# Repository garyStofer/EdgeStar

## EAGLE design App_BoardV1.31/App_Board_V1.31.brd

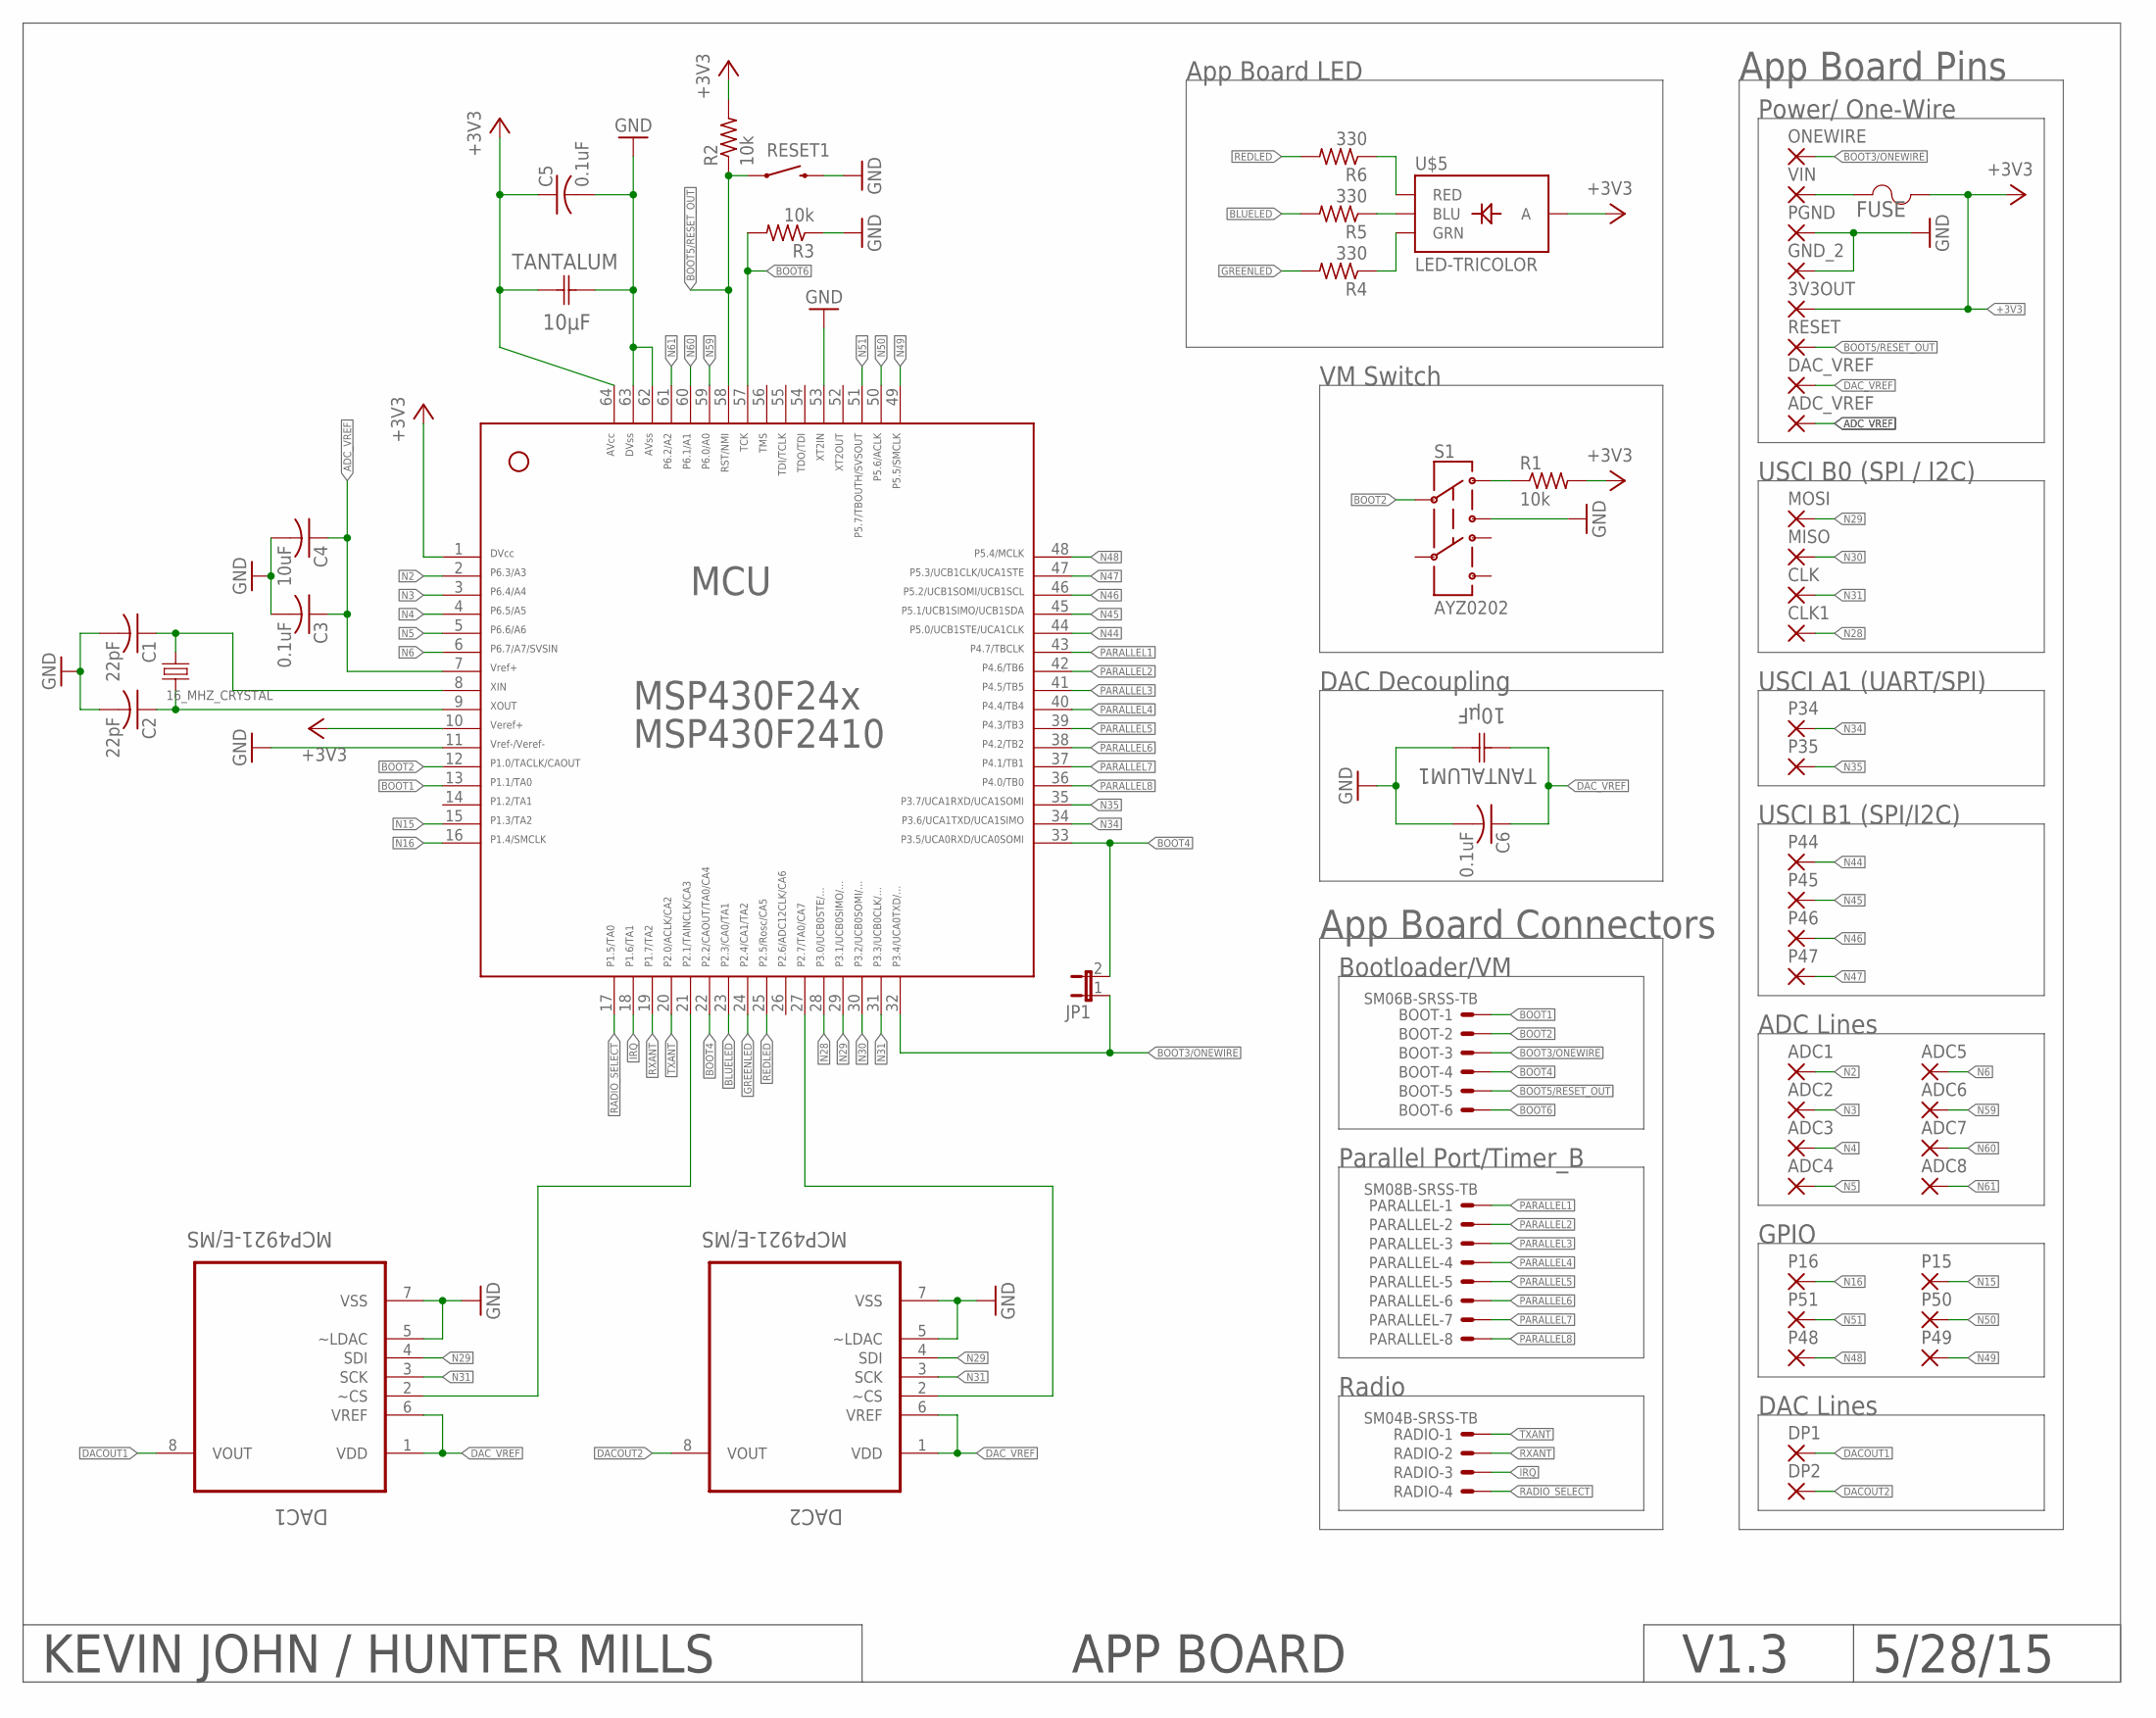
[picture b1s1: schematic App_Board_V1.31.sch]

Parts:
3V3OUT: 1,6/0,9
16_MHZ_CRYSTAL: HUNTERCRYSTAL; CRYSTAL-SMD-5X3
ADC1, ADC2, ADC3, ADC4, ADC5, ADC6, ADC7, ADC8: 1,6/0,9
ADC_VREF: 1,6/0,9
BOOT: SM06B-SRSS-TB
C1, C2: 22pF; C0805
C3, C5, C6: 0.1uF; C0805
C4: 10uF; C0805
CLK, CLK1: 1,6/0,9
DAC1, DAC2: MCP4921-E/MS; SOP65P490X110-8N
DAC_VREF: 1,6/0,9
DP1, DP2: 1,6/0,9
FUSE: HUNTERFUSE; CAPC4532X254N
GND_2: 1,6/0,9
JP1: JP1E; JP1
MCU: F24[X/10]---PM64; PM/PAG64
MISO: 1,6/0,9
MOSI: 1,6/0,9
ONEWIRE: 1,6/0,9
P15, P16, P34, P35, P44, P45, P46, P47, P48, P49, P50, P51: 1,6/0,9
PARALLEL: SM08B-SRSS-TB
PGND: 1,6/0,9
R1, R2, R3: 10k; R0603
R4, R5, R6: 330; R0603
RADIO: SM04B-SRSS-TB
RESET: 1,6/0,9
RESET1: SWITCH-MOMENTARY-2SMD; TACTILE-SWITCH-SMD
S1: AYZ0202
TANTALUM, TANTALUM1: 10µF; CAPCP3528X120N
U$5: LED-TRICOLOR; LED-TRICOLOR-SMD
VIN: 1,6/0,9

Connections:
3.3VOUT: FUSE.1, VIN.1
+3V3: 3V3OUT.1, C5.1, FUSE.2, MCU.1, MCU.10, MCU.64, R1.2, R2.2, TANTALUM.1 (C1), U$5.A
ADC_VREF: ADC_VREF.1, C3.1, C4.1, MCU.7
BLUELED: MCU.23, R5.2
BOOT1: BOOT.1, MCU.13
BOOT2: BOOT.2, MCU.12, S1.2
BOOT3/ONEWIRE: BOOT.3, JP1.1, MCU.32, ONEWIRE.1
BOOT4: BOOT.4, JP1.2, MCU.22, MCU.33
BOOT5/RESET_OUT: BOOT.5, MCU.58, R2.1, RESET.1, RESET1.1
BOOT6: BOOT.6, MCU.57, R3.2
DACOUT1: DAC1.8 (VOUT), DP1.1
DACOUT2: DAC2.8 (VOUT), DP2.1
DAC_VREF: C6.1, DAC1.1 (VDD), DAC1.6 (VREF), DAC2.1 (VDD), DAC2.6 (VREF), DAC_VREF.1, TANTALUM1.1 (C1)
GND: C1.2, C2.2, C3.2, C4.2, C5.2, C6.2, DAC1.5 (~LDAC), DAC1.7 (VSS), DAC2.5 (~LDAC), DAC2.7 (VSS), GND_2.1, MCU.11, MCU.53, MCU.62, MCU.63, PGND.1, R3.1, RESET1.3 (2), S1.1 (3), TANTALUM.2 (C2), TANTALUM1.2 (C2)
GREENLED: MCU.24, R4.2
IRQ: MCU.18, RADIO.3
N2: ADC1.1, MCU.2
N3: ADC2.1, MCU.3
N4: ADC3.1, MCU.4
N5: ADC4.1, MCU.5
N6: ADC5.1, MCU.6
N15: MCU.15, P15.1
N16: MCU.16, P16.1
N28: CLK1.1, MCU.28
N29: DAC1.4 (SDI), DAC2.4 (SDI), MCU.29, MOSI.1
N30: MCU.30, MISO.1
N31: CLK.1, DAC1.3 (SCK), DAC2.3 (SCK), MCU.31
N34: MCU.34, P34.1
N35: MCU.35, P35.1
N44: MCU.44, P44.1
N45: MCU.45, P45.1
N46: MCU.46, P46.1
N47: MCU.47, P47.1
N48: MCU.48, P48.1
N49: MCU.49, P49.1
N50: MCU.50, P50.1
N51: MCU.51, P51.1
N59: ADC6.1, MCU.59
N60: ADC7.1, MCU.60
N61: ADC8.1, MCU.61
unnamed: 16_MHZ_CRYSTAL.3, C1.1, MCU.8
unnamed: 16_MHZ_CRYSTAL.1, C2.1, MCU.9
unnamed: R1.1, S1.3 (1)
unnamed: R5.1, U$5.B (BLU)
unnamed: R6.1, U$5.R (RED)
unnamed: R4.1, U$5.G (GRN)
unnamed: DAC1.2 (~CS), MCU.21
unnamed: DAC2.2 (~CS), MCU.27
PARALLEL1: MCU.43, PARALLEL.1
PARALLEL2: MCU.42, PARALLEL.2
PARALLEL3: MCU.41, PARALLEL.3
PARALLEL4: MCU.40, PARALLEL.4
PARALLEL5: MCU.39, PARALLEL.5
PARALLEL6: MCU.38, PARALLEL.6
PARALLEL7: MCU.37, PARALLEL.7
PARALLEL8: MCU.36, PARALLEL.8
RADIO_SELECT: MCU.17, RADIO.4
REDLED: MCU.25, R6.2
RXANT: MCU.19, RADIO.2
TXANT: MCU.20, RADIO.1

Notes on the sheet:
KEVIN JOHN / HUNTER MILLS
APP BOARD
V1.3
5/28/15
Power/ One-Wire
ADC Lines
DAC Lines
USCI B0 (SPI / I2C)
USCI A1 (UART/SPI)
USCI B1 (SPI/I2C)
GPIO
App Board Pins
Bootloader/VM
Parallel Port/Timer_B
Radio
App Board Connectors
App Board LED
VM Switch
DAC Decoupling

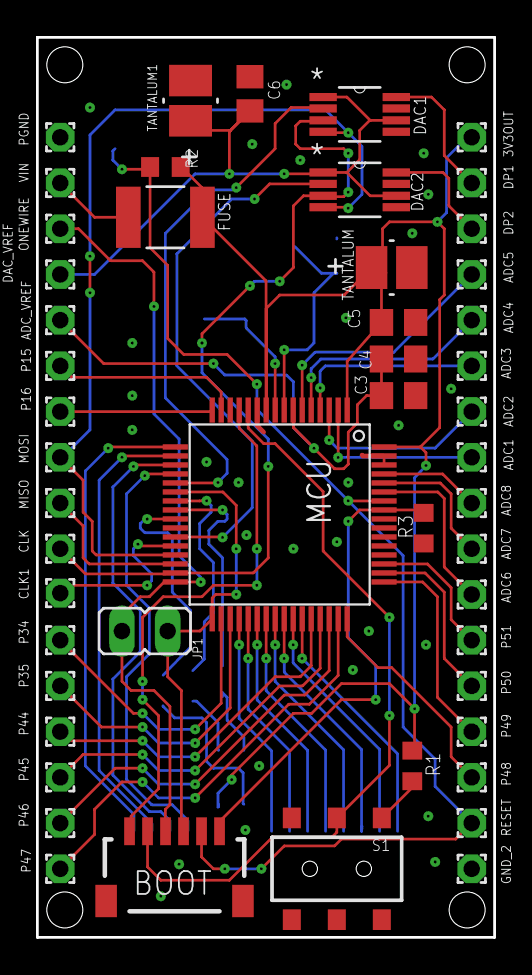
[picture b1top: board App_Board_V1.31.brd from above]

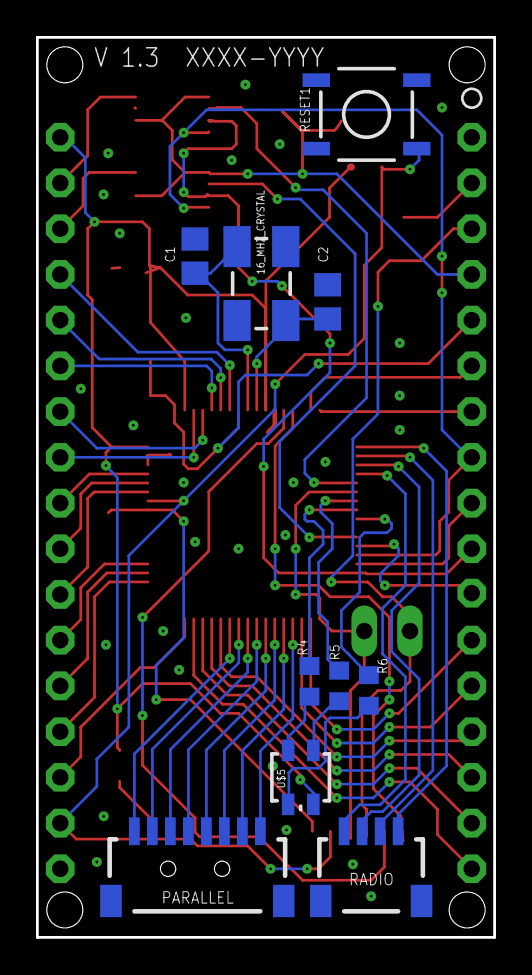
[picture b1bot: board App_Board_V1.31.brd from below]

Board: 2 copper layers, 25.4 x 50.0 mm, 60 parts (10 on the bottom side), 60 nets.

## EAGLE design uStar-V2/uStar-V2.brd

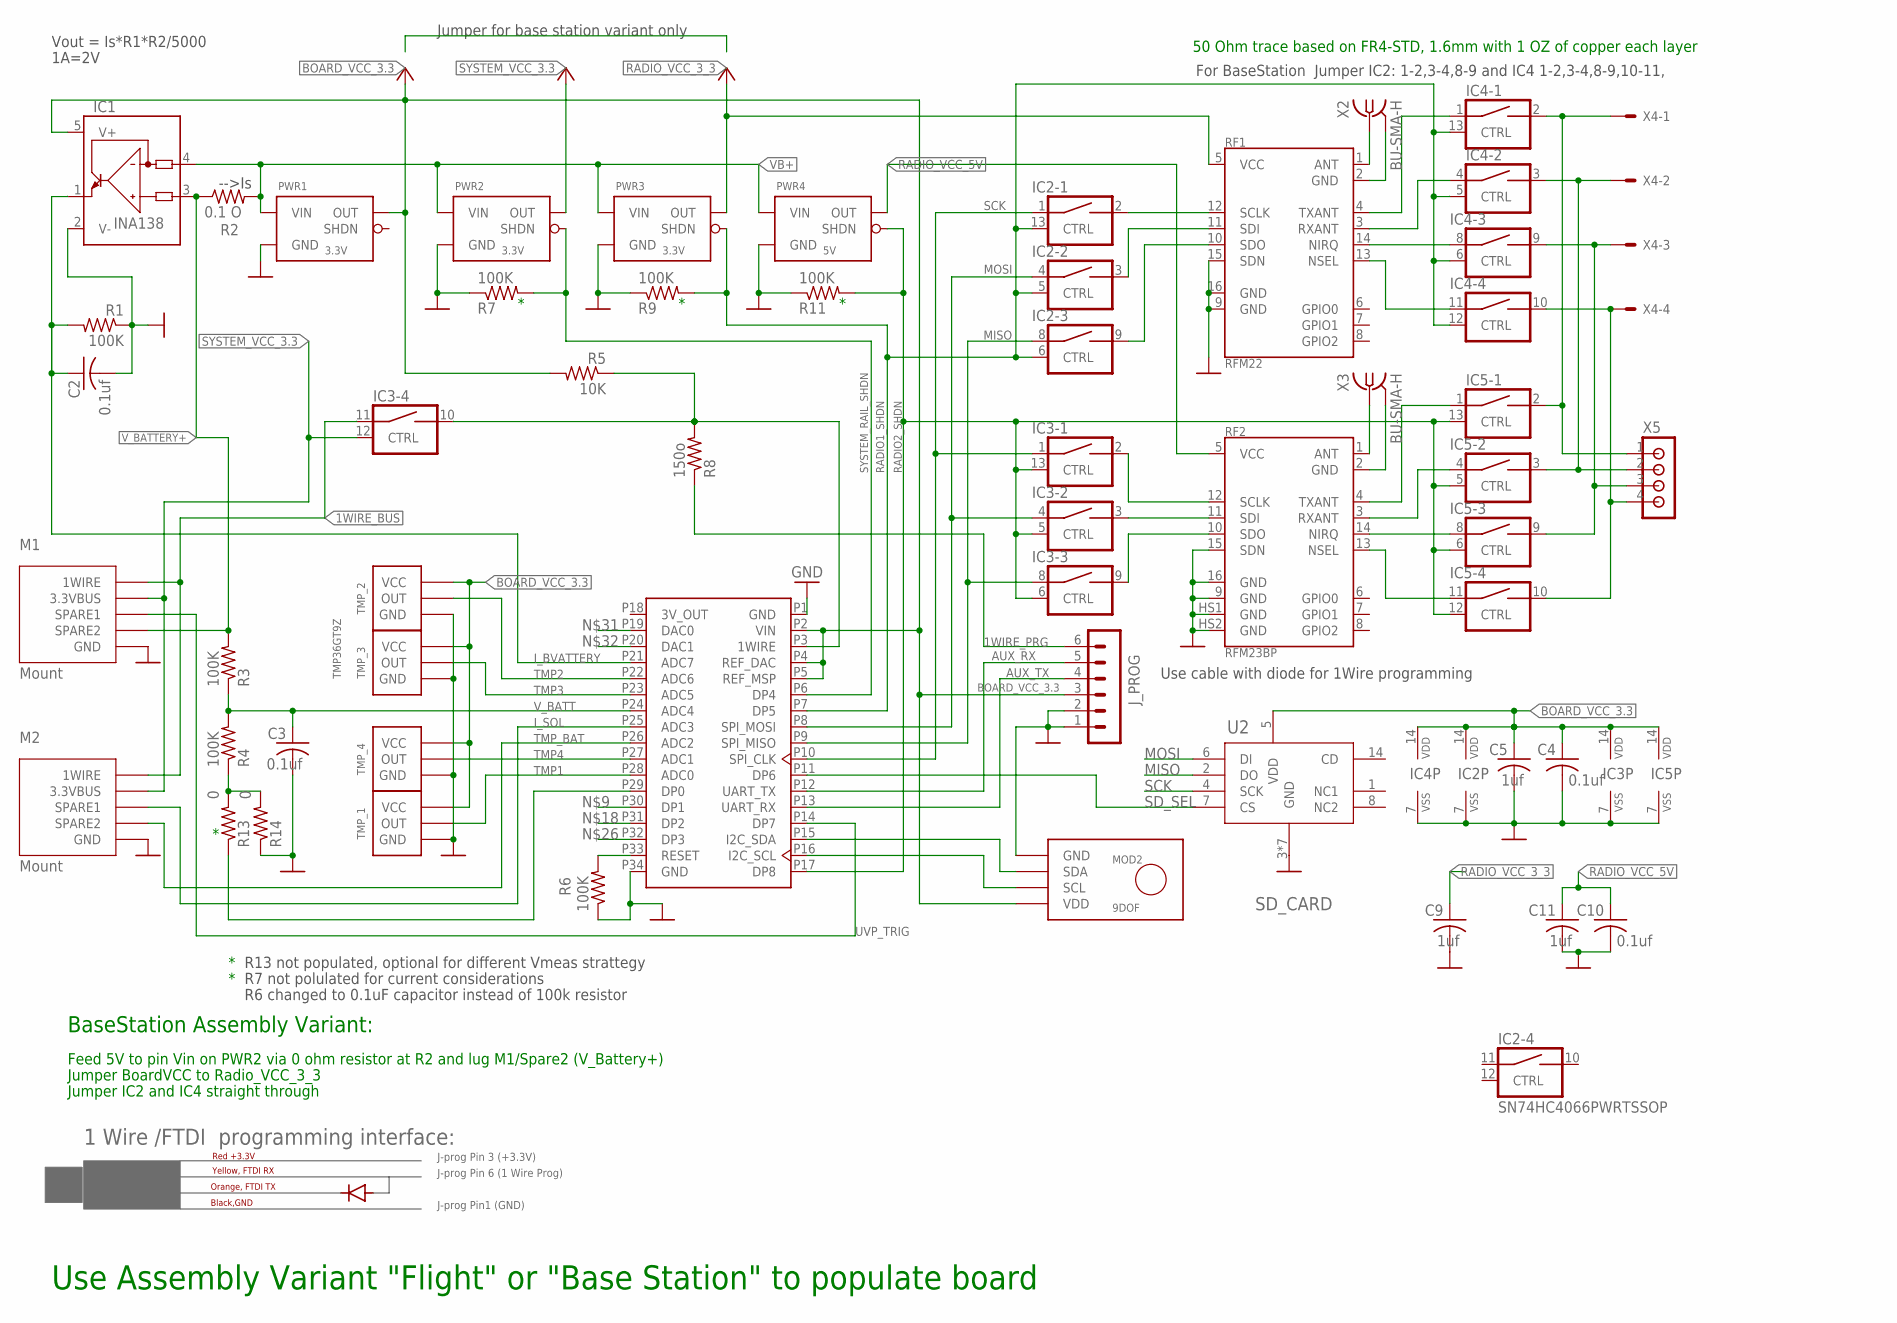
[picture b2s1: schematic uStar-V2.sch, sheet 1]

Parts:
C2, C4, C10: 0.1uf; C0805; DIGIKEY 1276-1099-1-ND
C3: 0.1uf; C0805; DIGIKEY 311-3497-1-ND
C5, C9, C11: 1uf; C0805; DIGIKEY 311-3497-1-ND
D1: 1N4148DO35-7; DO35-7
IC1: INA138; SOT23-5; DIGIKEY 296-17936-2-ND
IC2, IC3, IC4, IC5: SN74HC4066PWRTSSOP; TSSOP14
J_PROG: 90deg header; MA06-1-90; DIGIKEY 2057-PH1R8-06-UA-ND
M1, M2: Mount; 4X8MOUNT
MOD1: APP_CORE; APPCORE_RECEIVER; DIGIKEY S7050-ND Two times
MOD2: 9DOF; DIGIKEY 1568-1424-ND
PWR1, PWR2, PWR3: 3.3V; S7V_UP; DIGIKEY 2183-2122-ND
PWR4: 5V; S10_UP; DIGIKEY 2183-2121-ND
R1, R3, R4, R6, R7, R9, R11: 100K; R0805; DIGIKEY 2019-RK73H2ATTD1003FCT-ND
R2: 0.1 O; R1206W; DIGIKEY CSR1206FTR100CT-ND
R5: 10K; R0805; DIGIKEY 311-10.0KCRCT-ND
R8: 150o; R0805; DIGIKEY 2019-RK73H2ATTD1200FCT-ND
R13, R14: 0; R0805; DIGIKEY 311-0.0ARCT-ND
RF1: RFM22
RF2: RFM23BP
TMP_1, TMP_4: TMP3P
TMP_2: TMP3P; DIGIKEY TMP36GT9Z-ND
TMP_3: TMP36GT9Z; TO92-INLINE
U2: SD_CARD; 503182-1852_MOL
X2, X3: BU-SMA-H; DIGIKEY WM4088-ND
X4: SM04B-SRSS-TB; DIGIKEY 455-1804-1-ND
X5: 4-TP; 1X04-1.5MM_JST

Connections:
1WIRE: IC3.10 (B), MOD1.P3 (1WIRE), R5.1, R8.2
1WIRE_BUS: IC3.11 (A), M1.P$2 (1WIRE), M1.P$5 (1WIRE), M2.P$2 (1WIRE), M2.P$5 (1WIRE)
1WIRE_PRG: J_PROG.6, R8.1
AUX_RX: J_PROG.5, MOD1.P12 (UART_TX)
AUX_TX: J_PROG.4, MOD1.P13 (UART_RX)
BOARD_VCC_3.3: C4.1, C5.1, IC1.5 (V+), IC2.14 (VDD), IC3.14 (VDD), IC4.14 (VDD), IC5.14 (VDD), J_PROG.3, MOD1.P2 (VIN), MOD1.P4 (REF_DAC), MOD1.P5 (REF_MSP), MOD2.VDD, PWR1.VOUT (OUT), R5.2, TMP_1.P$3 (VCC), TMP_2.P$3 (VCC), TMP_3.1 (VCC), TMP_4.P$3 (VCC), U2.5 (VDD)
GND: C2.2, C3.2, C4.2, C5.2, C9.2, C10.2, C11.2, IC1.2 (V-), IC2.7 (VSS), IC3.7 (VSS), IC4.7 (VSS), IC5.7 (VSS), J_PROG.1, J_PROG.2, M1.P$1 (GND), M1.P$8 (GND), M2.P$1 (GND), M2.P$8 (GND), MOD1.P1 (GND), MOD1.P34 (GND), MOD2.GND, PWR1.GND, PWR2.GND, PWR3.GND, PWR4.GND, R1.1, R6.1, R7.1, R9.1, R11.1, R14.1, RF1.2 (GND), RF1.9 (GND), RF1.15 (SDN), RF1.16 (GND), RF2.2 (GND), RF2.9 (GND), RF2.15 (SDN), RF2.16 (GND), RF2.HS1 (GND), RF2.HS2 (GND), TMP_1.P$1 (GND), TMP_2.P$1 (GND), TMP_3.3 (GND), TMP_4.P$1 (GND), U2.3 (GND), U2.9 (GND), U2.10 (GND), U2.11 (GND), U2.12 (GND), U2.13 (GND), U2.15 (GND), X2.2, X2.3 (2), X2.4 (2), X2.5 (2), X3.2, X3.3 (2), X3.4 (2), X3.5 (2)
I_BVATTERY: C2.1, IC1.1 (OUT), MOD1.P21 (ADC7), R1.2
I_SOL: M2.P$6 (SPARE1), MOD1.P25 (ADC3)
MISO: IC2.8 (A), IC3.8 (A), MOD1.P9 (SPI_MISO), U2.2 (DO)
MOSI: IC2.4 (A), IC3.4 (A), MOD1.P8 (SPI_MOSI), U2.6 (DI)
unnamed: MOD1.P16 (I2C_SCL), MOD2.SCL
unnamed: MOD1.P15 (I2C_SDA), MOD2.SDA
unnamed: RF1.1 (ANT), X2.1
unnamed: RF2.1 (ANT), X3.1
unnamed: IC5.8 (A), RF2.14 (NIRQ)
unnamed: MOD1.P29 (DP0), R13.1
unnamed: IC2.2 (B), RF1.12 (SCLK)
unnamed: IC4.8 (A), RF1.14 (NIRQ)
unnamed: IC2.3 (B), RF1.11 (SDI)
unnamed: IC2.9 (B), RF1.10 (SDO)
unnamed: MOD1.P33 (RESET), R6.2
unnamed: IC3.2 (B), RF2.12 (SCLK)
unnamed: IC3.3 (B), RF2.11 (SDI)
unnamed: IC3.9 (B), RF2.10 (SDO)
unnamed: IC4.9 (B), IC5.9 (B), X4.3, X5.3
unnamed: IC5.11 (A), RF2.13 (NSEL)
unnamed: IC4.4 (A), RF1.3 (RXANT)
unnamed: IC4.10 (B), IC5.10 (B), X4.4, X5.4
unnamed: IC5.1 (A), RF2.4 (TXANT)
unnamed: IC4.3 (B), IC5.3 (B), X4.2, X5.2
unnamed: IC4.2 (B), IC5.2 (B), X4.1, X5.1
unnamed: R4.1, R13.2, R14.2
NIRQ: IC4.11 (A), RF1.13 (NSEL)
RADIO1_SHDN: IC2.5 (CTRL), IC2.6 (CTRL), IC2.13 (CTRL), IC4.5 (CTRL), IC4.6 (CTRL), IC4.12 (CTRL), IC4.13 (CTRL), MOD1.P7 (DP5), PWR3.SHDN, R9.2
RADIO2_SHDN: IC3.5 (CTRL), IC3.6 (CTRL), IC3.13 (CTRL), IC5.5 (CTRL), IC5.6 (CTRL), IC5.12 (CTRL), IC5.13 (CTRL), MOD1.P17 (DP8), PWR4.SHDN, R11.2
RADIO_VCC_3_3: C9.1, PWR3.VOUT (OUT), RF1.5 (VCC)
RADIO_VCC_5V: C10.1, C11.1, PWR4.VOUT (OUT), RF2.5 (VCC)
RXANT: IC5.4 (A), RF2.3 (RXANT)
SCK: IC2.1 (A), IC3.1 (A), MOD1.P10 (SPI_CLK), U2.4 (SCK)
SD_SEL: MOD1.P11 (DP6), U2.7 (CS)
SYSTEM_RAIL_SHDN: MOD1.P6 (DP4), PWR2.SHDN, R7.2
SYSTEM_VCC_3.3: IC3.12 (CTRL), M1.P$4 (3.3VBUS), M1.P$7 (3.3VBUS), M2.P$4 (3.3VBUS), M2.P$7 (3.3VBUS), PWR2.VOUT (OUT)
TMP1: MOD1.P28 (ADC0), TMP_1.P$2 (OUT)
TMP2: MOD1.P22 (ADC6), TMP_2.P$2 (OUT)
TMP3: MOD1.P23 (ADC5), TMP_3.2 (OUT)
TMP4: MOD1.P27 (ADC1), TMP_4.P$2 (OUT)
TMP_BAT: M2.P$3 (SPARE2), MOD1.P26 (ADC2)
TXANT: IC4.1 (A), RF1.4 (TXANT)
UVP_TRIG: M1.P$6 (SPARE1), MOD1.P14 (DP7)
VB+: IC1.4 (IN-), PWR1.VIN, PWR2.VIN, PWR3.VIN, PWR4.VIN, R2.2
V_BATT: C3.1, MOD1.P24 (ADC4), R3.1, R4.2
V_BATTERY+: IC1.3 (IN+), M1.P$3 (SPARE2), R2.1, R3.2

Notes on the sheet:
Vout = Is*R1*R2/5000
-->Is
1A=2V
Use cable with diode for 1Wire programming
50 Ohm trace based on FR4-STD, 1.6mm with 1 OZ of copper each layer
R13 not populated, optional for different Vmeas strattegy
Jumper BoardVCC to Radio_VCC_3_3
Jumper IC2 and IC4 straight through
Feed 5V to pin Vin on PWR2 via 0 ohm resistor at R2 and lug M1/Spare2 (V_Battery+)
BaseStation Assembly Variant:
Jumper for base station variant only
Use Assembly Variant "Flight" or "Base Station" to populate board
R7 not polulated for current considerations
For BaseStation Jumper IC2: 1-2,3-4,8-9 and IC4 1-2,3-4,8-9,10-11,
1 Wire /FTDI programming interface:
Red +3.3V
Yellow, FTDI RX
Orange, FTDI TX
Black,GND
J-prog Pin1 (GND)
J-prog Pin 6 (1 Wire Prog)
J-prog Pin 3 (+3.3V)
R6 changed to 0.1uF capacitor instead of 100k resistor

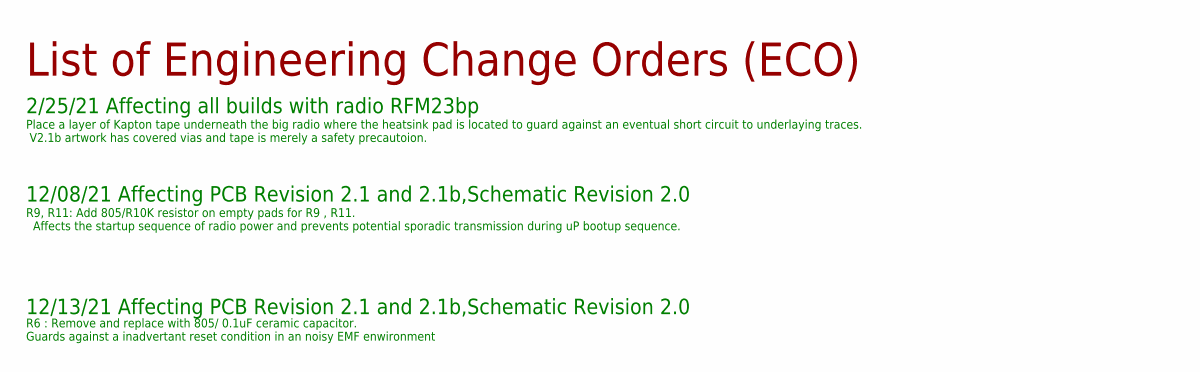
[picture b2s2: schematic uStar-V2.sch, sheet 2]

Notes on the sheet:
List of Engineering Change Orders (ECO)
12/13/21 Affecting PCB Revision 2.1 and 2.1b,Schematic Revision 2.0
R6 : Remove and replace with 805/ 0.1uF ceramic capacitor. Guards against a inadvertant reset condition in an noisy EMF enwironment
12/08/21 Affecting PCB Revision 2.1 and 2.1b,Schematic Revision 2.0
R9, R11: Add 805/R10K resistor on empty pads for R9 , R11. Affects the startup sequence of radio power and prevents potential sporadic transmission during uP bootup sequence.
2/25/21 Affecting all builds with radio RFM23bp
Place a layer of Kapton tape underneath the big radio where the heatsink pad is located to guard against an eventual short circuit to underlaying traces. V2.1b artwork has covered vias and tape is merely a safety precautoion.

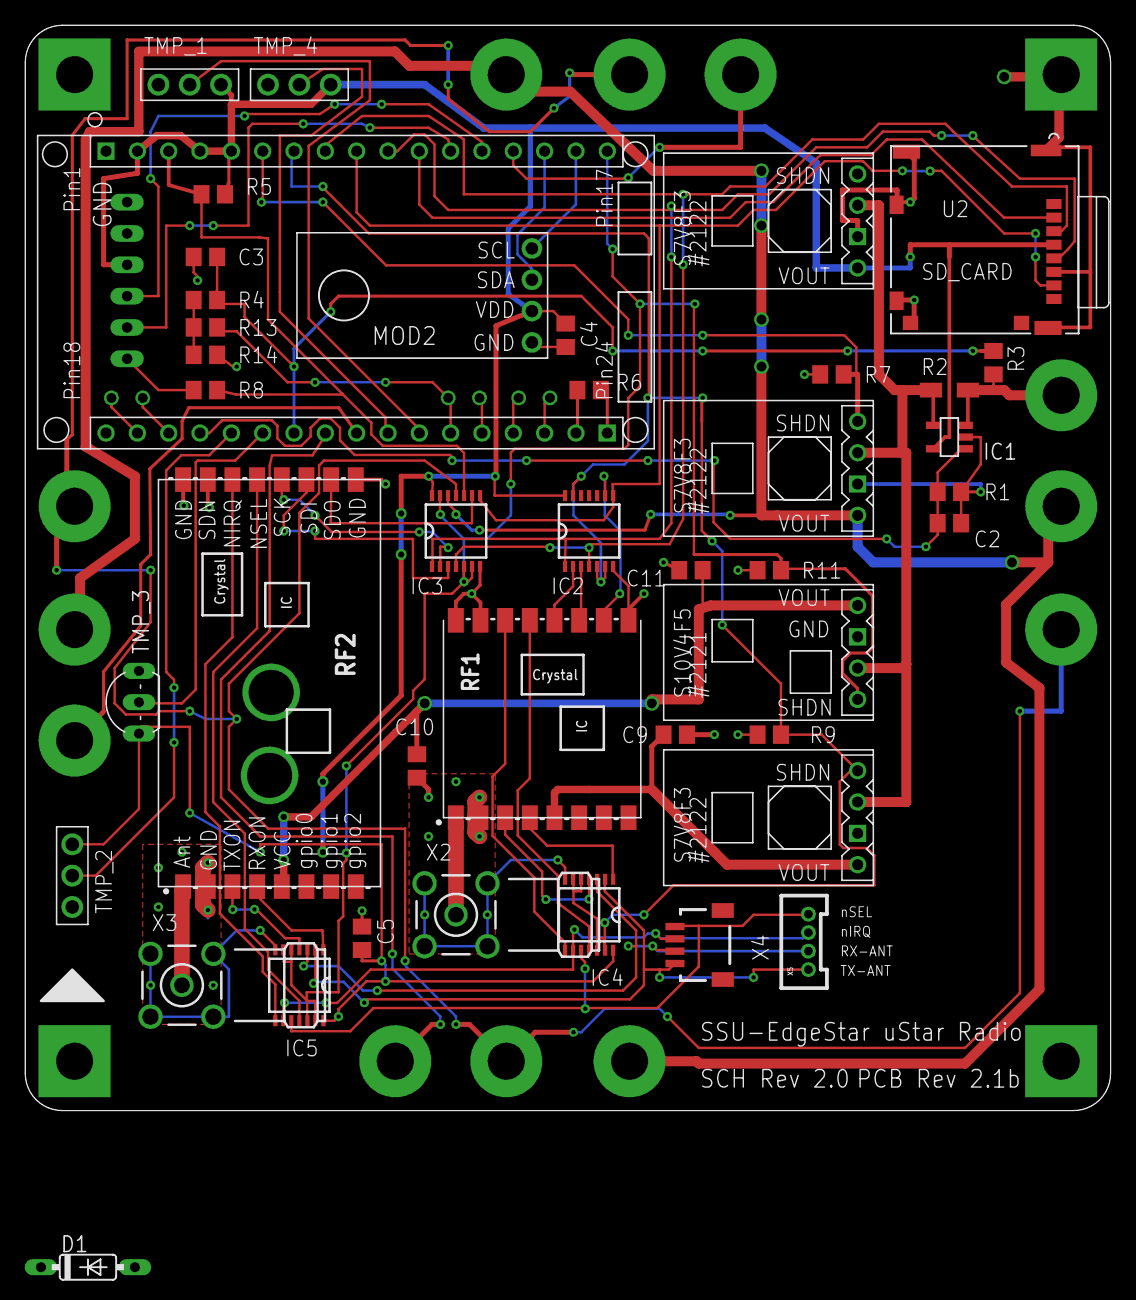
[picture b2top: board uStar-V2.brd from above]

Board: 2 copper layers, 88.0 x 88.0 mm, 46 parts (1 on the bottom side), 53 nets.

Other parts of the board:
U$1: PCBOUTLINE

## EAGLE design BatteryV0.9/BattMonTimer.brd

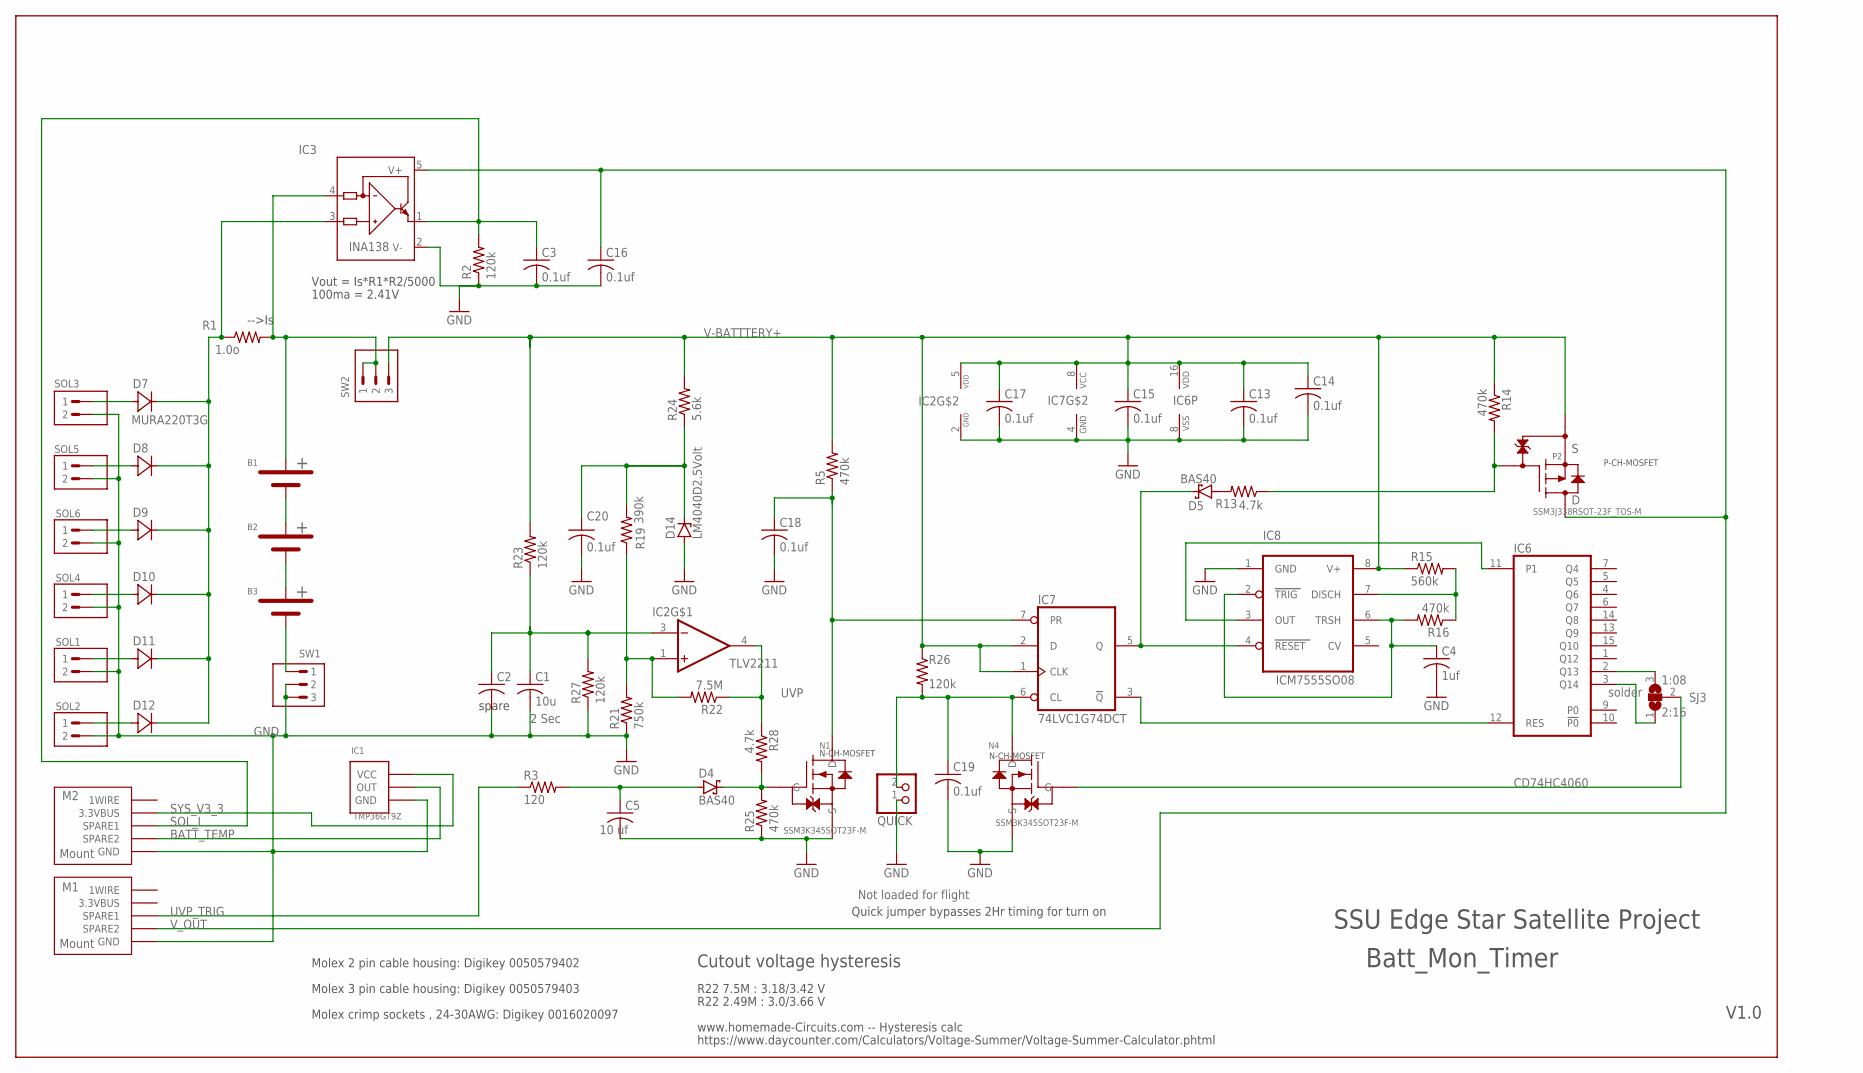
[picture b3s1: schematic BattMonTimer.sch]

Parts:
B1, B2, B3: AA-BATT
C1: 10u; C0805; DIGIKEY 490-14381-1-ND
C2: C-USC0805; C0805; DIGIKEY 490-14381-1-ND
C3, C13, C14, C15, C16, C17, C18, C19, C20: 0.1uf; C0805; DIGIKEY 1276-1099-1-ND
C4: 1uf; C0805; DIGIKEY 311-3497-1-ND
C5: 10 uf; C0805; DIGIKEY 490-14381-1-ND
D4, D5: BAS40; SOT23; DIGIKEY BAS40-04FDICT-ND
D7, D8, D9, D10, D11, D12: MURA220T3G; SMA
D14: LM4040D2.5Volt; SOT23
IC1: TMP36GT9Z; TO92-INLINE
IC2: TLV2211; SOT23-5
IC3: INA138; SOT23-5; DIGIKEY 296-17936-2-ND
IC6: CD74HC4060; SO16; DIGIKEY 296-25999-1-ND
IC7: 74LVC1G74DCT; DCT_R-PDSO-G8; DIGIKEY SN74LVC1G74DCTR
IC8: ICM7555SO08; SO08
M1, M2: Mount; 4X8MOUNT
N1, N4: SSM3K345SOT23F-M; SOT-23F_TOS-M
P2: SSM3J338RSOT-23F_TOS-M; SOT-23F_TOS-M
QUICK: Quick Start; 1X02
R1: 1.0o; R1206W; DIGIKEY RNCP1204FTD1R00CT-ND
R2, R23, R26, R27: 120k; R0805; DIGIKEY 2019-RK73H2ATTD1203FCT-ND
R3: 120; R0805; DIGIKEY 311-4.7KARCT-ND
R5, R14, R16, R25: 470k; R0805; DIGIKEY 2019-RK73H2ATTD4703FCT-ND
R13, R28: 4.7k; R0805; DIGIKEY 311-4.7KARCT-ND
R15: 560k; R0805; DIGIKEY 2019-RK73H2ATTD5603FCT-ND
R19: 390k; R0805; DIGIKEY RK73H2ATTD3903FCT-ND
R21: 750k; R0805; DIGIKEY 2019-RK73H2ATTD7503FCT-ND
R22: 7.5M; R0805; DIGIKEY 541-7.50MCCT-ND
R24: 5.6k; R0805; DIGIKEY 2019-RK73H2ATTD5601FCT-ND
SJ3: solder; SJ_2
SOL1, SOL2, SOL3, SOL4, SOL5, SOL6: MOLEX2PINHDR; MOLEX2PIN
SW1, SW2: MOLEX3PINHDR; MOLEX3PIN

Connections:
BATT_TEMP: IC1.2 (OUT), M2.P$3 (SPARE2)
GND: C1.2, C2.2, C3.2, C4.2, C5.2, C13.2, C14.2, C15.2, C16.2, C17.2, C18.2, C19.2, C20.2, D14.2 (A), IC1.3 (GND), IC2.2 (VDD_GND), IC3.2 (V-), IC6.8 (VSS), IC7.4 (GND), IC8.1 (GND), M1.P$1 (GND), M1.P$8 (GND), M2.P$1 (GND), M2.P$8 (GND), N1.2 (S), N4.2 (S), QUICK.1, R2.1, R21.1, R25.1, R27.1, SOL1.P$2 (2), SOL2.P$2 (2), SOL3.P$2 (2), SOL4.P$2 (2), SOL5.P$2 (2), SOL6.P$2 (2), SW1.P$2 (2), SW1.P$3 (3)
unnamed: B1.PLUS (+), IC3.4 (IN-), R1.2, SW2.P$1 (1), SW2.P$2 (2)
unnamed: D7.C, D8.C, D9.C, D10.C, D11.C, D12.C, IC3.3 (IN+), R1.1
unnamed: C5.1, D4.1 (A), R3.2
unnamed: D7.A, SOL3.P$1 (1)
unnamed: D8.A, SOL5.P$1 (1)
unnamed: D9.A, SOL6.P$1 (1)
unnamed: D10.A, SOL4.P$1 (1)
unnamed: D11.A, SOL1.P$1 (1)
unnamed: D12.A, SOL2.P$1 (1)
unnamed: B3.MINUS (-), SW1.P$1 (1)
unnamed: B2.MINUS (-), B3.PLUS (+)
unnamed: B1.MINUS (-), B2.PLUS (+)
unnamed: D5.3 (C), IC7.5 (Q), IC8.4 (RESET)
unnamed: N4.1 (G), SJ3.2
unnamed: D5.1 (A), R13.2
unnamed: P2.1, R13.1, R14.2
unnamed: IC6.2 (Q13), SJ3.3
unnamed: IC2.1 (+IN), R19.1, R21.2, R22.2
unnamed: C1.1, C2.1, IC2.3 (-IN), R23.1, R27.2
unnamed: C19.1, IC7.6 (CL), N4.3 (D), QUICK.2, R26.2
unnamed: IC6.12 (RES), IC7.3 (!Q)
unnamed: D4.3 (C), N1.1 (G), R25.2, R28.2
unnamed: C20.1, D14.1 (C), R19.2, R24.1
unnamed: C4.1, IC8.2 (TRIG), IC8.6 (TRSH), R16.2
unnamed: IC8.7 (DISCH), R15.2, R16.1
unnamed: IC6.11 (P1), IC8.3 (OUT)
unnamed: IC6.3 (Q14), SJ3.1
SOL_I: C3.1, IC3.1 (OUT), M2.P$6 (SPARE1), R2.2
SYS_V3_3: IC1.1 (VCC), M2.P$4 (3.3VBUS), M2.P$7 (3.3VBUS)
UVP: IC2.4 (OUT), R22.1, R28.1
UVP_1: C18.1, IC7.7 (PR), N1.3 (D), R5.1
UVP_TRIG: M1.P$6 (SPARE1), R3.1
V-BATTTERY+: C13.1, C14.1, C15.1, C17.1, IC2.5 (VDD), IC6.16 (VDD), IC7.1 (CLK), IC7.2 (D), IC7.8 (VCC), IC8.8 (V+), P2.2, R5.2, R14.1, R15.1, R23.2, R24.2, R26.1, SW2.P$3 (3)
V_OUT: C16.1, IC3.5 (V+), M1.P$3 (SPARE2), P2.3

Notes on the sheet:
SSU Edge Star Satellite Project
P-CH-MOSFET
N-CH-MOSFET
www.homemade-Circuits.com -- Hysteresis calc
1:08
2:16
2 Sec
Cutout voltage hysteresis
V1.0
Vout = Is*R1*R2/5000
-->Is
100ma = 2.41V
Batt_Mon_Timer
Molex 2 pin cable housing: Digikey 0050579402
Molex 3 pin cable housing: Digikey 0050579403
Molex crimp sockets , 24-30AWG: Digikey 0016020097
Quick jumper bypasses 2Hr timing for turn on
spare
https://www.daycounter.com/Calculators/Voltage-Summer/Voltage-Summer-Calculator.phtml
R22 2.49M : 3.0/3.66 V
R22 7.5M : 3.18/3.42 V

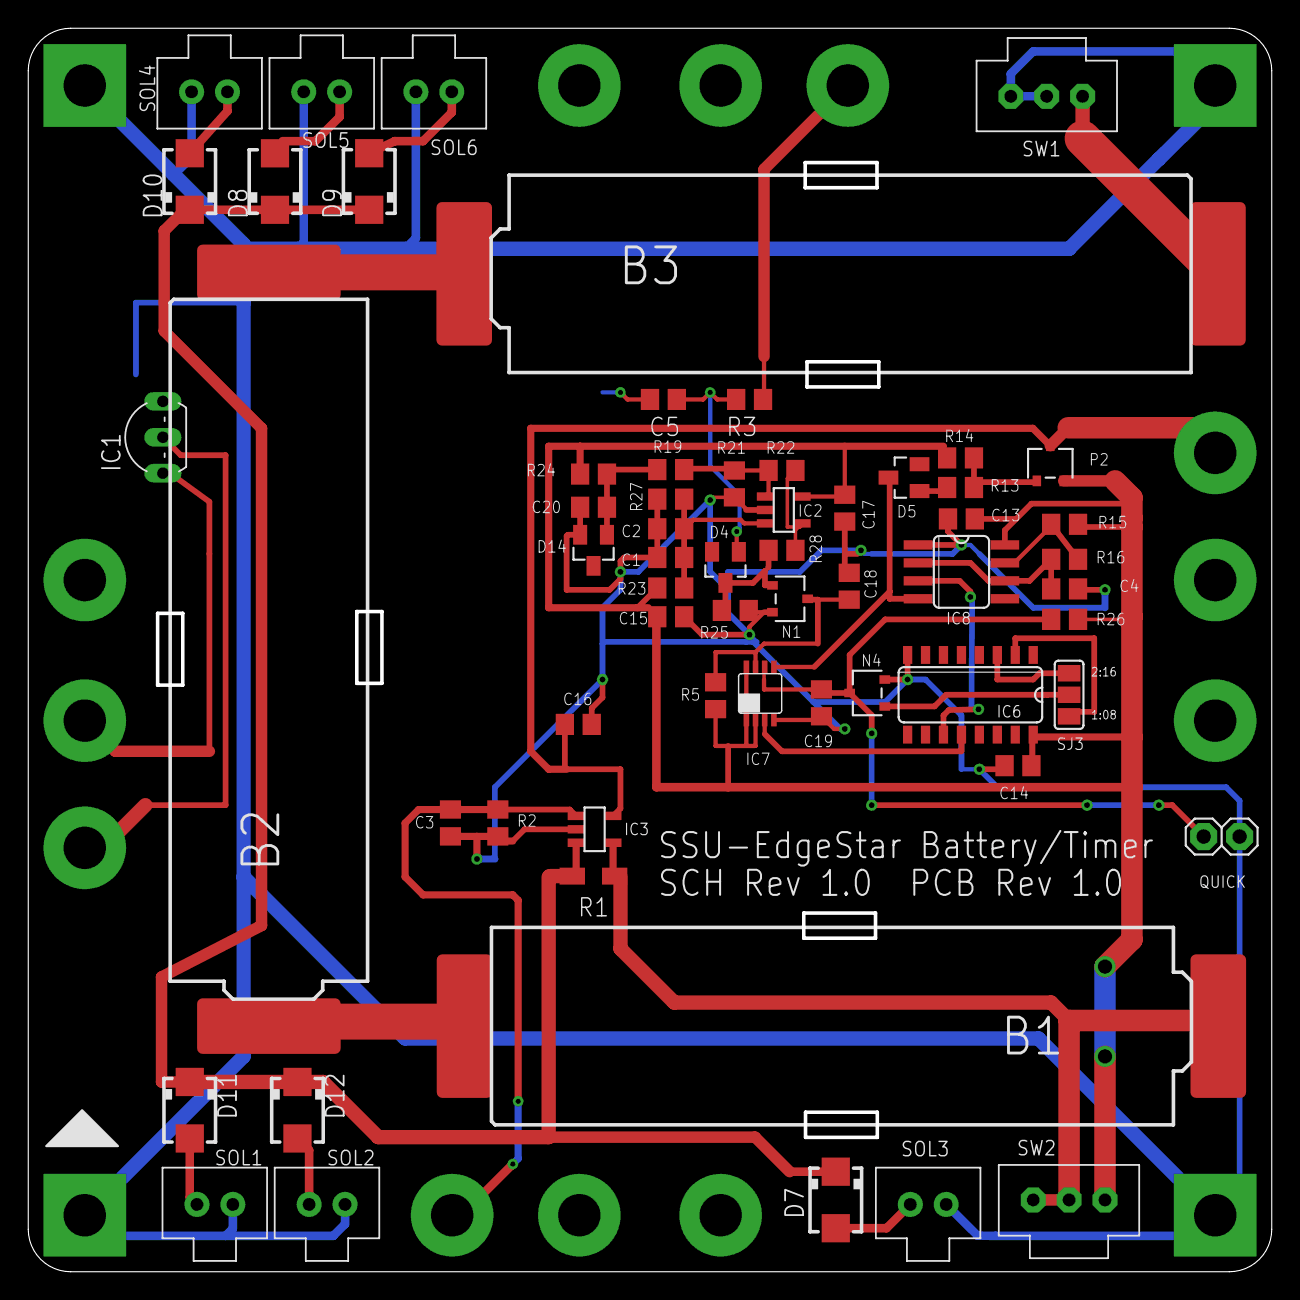
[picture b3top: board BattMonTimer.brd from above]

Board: 2 copper layers, 88.0 x 88.0 mm, 63 parts (0 on the bottom side), 36 nets.

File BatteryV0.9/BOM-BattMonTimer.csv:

"Qty";"Value";"Device";"Package";"Parts";"Description";"DIGIKEY";"MANUFACTURER_PART_NUMBER";"MF";"MPN";"NOTPOPULATED";"NO_PN";"OC_FARNELL";"OC_NEWARK";"POPULARITY";"PRIORITY";"SOURCELIBRARY";"SPICEPREFIX";"TYPE";"VALUE";"VENDOR";
"9";"0.1uf";"C-USC0805";"C0805";"C3, C13, C14, C15, C16, C17, C18, C19, C20";"CAPACITOR, American symbol";"1276-1099-1-ND";"";"";"";"";"";"";"";"63";"";"";"C";"";"";"";
"1";"10 uf ,XR7";"C-USC0805";"C0805";"C1";"CAPACITOR, American symbol";"490-14381-1-ND";"";"";"";"";"";"";"";"63";"";"";"C";"";"";"";
"1";"120k";"R-US_R0805";"R0805";"R23";"RESISTOR, American symbol";"2019-RK73H2ATTD1203FCT-ND ";"";"";"";"";"";"";"";"85";"";"";"R";"";"";"";
"3";"120k";"R-US_R0805";"R0805";"R2, R26, R27";"RESISTOR, American symbol";"2019-RK73H2ATTD1203FCT-ND";"";"";"";"";"";"";"";"85";"";"";"R";"";"";"";
"1";"1o";"R-US_R0805";"R0805";"R1";"RESISTOR, American symbol";"RNCP0805FTD1R00CT-ND";"";"";"";"";"";"";"";"85";"";"";"R";"";"";"";
"1";"1uf";"C-USC0805";"C0805";"C4";"CAPACITOR, American symbol";"311-3497-1-ND";"";"";"";"";"";"";"";"63";"";"";"C";"X7R";"";"";
"1";"390k";"R-US_R0805";"R0805";"R19";"RESISTOR, American symbol";"RK73H2ATTD3903FCT-ND ";"";"";"";"";"";"";"";"85";"";"";"R";"";"";"";
"2";"4.7k";"R-US_R0805";"R0805";"R13, R28";"RESISTOR, American symbol";"311-4.7KARCT-ND";"";"";"";"";"";"";"";"85";"";"";"R";"";"";"";
"4";"470k";"R-US_R0805";"R0805";"R5, R14, R16, R25";"RESISTOR, American symbol";"2019-RK73H2ATTD4703FCT-ND";"";"";"";"";"";"";"";"85";"";"";"R";"";"";"";
"1";"5.6k";"R-US_R0805";"R0805";"R24";"RESISTOR, American symbol";"2019-RK73H2ATTD5601FCT-ND";"";"";"";"";"";"";"";"85";"";"";"R";"";"";"";
"1";"560k";"R-US_R0805";"R0805";"R15";"RESISTOR, American symbol";"2019-RK73H2ATTD5603FCT-ND";"";"";"";"";"";"";"";"85";"";"";"R";"";"";"";
"1";"7.5M";"R-US_R0805";"R0805";"R22";"RESISTOR, American symbol";"541-7.50MCCT-ND";"";"";"";"";"";"";"";"85";"";"";"R";"";"";"";
"1";"74LVC1G74DCT";"74LVC1G74DCT";"DCT_R-PDSO-G8";"IC7";"D type flipflo with async Set and Clear";"SN74LVC1G74DCTR";"";"";"";"";"";"";"";"";"";"";"";"";"";"";
"1";"750k";"R-US_R0805";"R0805";"R21";"RESISTOR, American symbol";"2019-RK73H2ATTD7503FCT-ND";"";"";"";"";"";"";"";"85";"";"";"R";"";"";"";
"3";"AA-BATT";"AA-BATT";"AA-BATT";"B1, B2, B3";"NiCD or NIMH battery AA formfactor with ziptie strapping option";"SY115T-ND";"";"";"";"";"";"";"";"";"";"";"";"";"";"";
"2";"BAS40";"BAS40";"SOT23";"D4, D5";"Silicon Schottky Diodes";"BAS40-04FDICT-ND ";"";"";"";"";"";"";"";"0";"";"";"";"";"";"";
"1";"CD74HC4060";"4060D";"SO16";"IC6";"14-stage binary/ripple COUNTER";"296-25999-1-ND";"";"";"";"";"";"";"";"0";"";"";"";"";"";"";
"1";"ICM7555SO08";"ICM7555SO08";"SO08";"IC8";"TIMER";"ICM7555CBAZ-TCT-ND";"";"";"";"";"";"";"";"";"";"";"";"";"";"";
"1";"INA138";"INA138";"SOT23-5";"IC3";"High-Side Measurement Current Shunt Monitor";"296-17936-2-ND";"";"TEXAS INSTRUMENTS";"INA138NA/250";"";"";"1564888";"80K5906";"0";"";"";"";"";"";"";
"1";"LM4040D2.5Volt";"LM4040";"SOT23";"D14";"";"LM4040D25FCT-ND";"";"";"";"";"";"";"";"";"";"";"";"";"";"";
"6";"MOLEX2PINHDR";"MOLEX2PINHDR";"MOLEX2PIN";"SOL1, SOL2, SOL3, SOL4, SOL5, SOL6";"molex 2 pin header with schroud and lock , pn 070543001";"0705430001";"";"";"";"";"";"";"";"";"";"";"";"";"";"";
"2";"MOLEX3PINHDR";"MOLEX3PINHDR";"MOLEX3PIN";"SW1, SW2";"Molex 3 pin header with shroud and lock PN:0705430002";"0705430002";"";"";"";"";"";"";"";"";"";"";"";"";"";"";
"6";"MURA220T3G";"MURA220T3G";"SMA";"D7, D8, D9, D10, D11, D12";"Surface Mount Schottky Power Rectifier";"MURA220T3GOSCT-ND";"";"";"";"";"";"";"";"9";"";"";"";"";"";"";
"2";"Mount";"4X8MOUNT";"4X8MOUNT";"M1, M2";"4x8 MOUNT for EDGEQUBE";"";"";"";"";"";"Hole pattern template";"";"";"";"";"";"";"";"Mount";"";
"1";"Quick Start";"PINHD-1X2";"1X02";"QUICK";"PIN HEADER";"";"";"";"";"Not loaded for flight";"";"";"";"";"";"";"";"";"";"";
"1";"SSM3J338RSOT-23F_TOS-M";"SSM3J338RSOT-23F_TOS-M";"SOT-23F_TOS-M";"P2";"";"SSM3J338RLFECT-ND";"SSM3J338R";"";"";"";"";"";"";"";"";"Toshiba_2018-12-14";"";"";"";"Toshiba";
"2";"SSM3K345SOT23F-M";"SSM3K345SOT23F-M";"SOT-23F_TOS-M";"N1, N4";"";"SSM3K345RLFCT-ND";"";"";"";"";"";"";"";"";"";"";"";"";"";"";
"1";"Spare,XR7";"C-USC0805";"C0805";"C2";"CAPACITOR, American symbol";"490-14381-1-ND";"";"";"";"";"";"";"";"63";"";"";"C";"";"";"";
"1";"TLV2211";"TLVB2211";"SOT23-5";"IC2";"TI Rail to Rail LINCMOS op-amp";"296-10500-1-ND";"";"";"";"";"";"";"";"";"";"";"";"";"";"";
"1";"TMP36GT9Z";"TMP36GT9Z";"TO92-INLINE";"IC1";"";"TMP36GT9Z-ND";"";"";"";"";"";"";"";"";"";"";"";"";"";"";
"1";"solder";"SJ2W";"SJ_2";"SJ3";"SMD solder JUMPER";"";"";"";"";"";"";"";"";"7";"";"";"";"";"";"";

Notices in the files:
parts and their libraries:
SparkFun-Electromechanical: Licensing: Creative Commons ShareAlike 4.0 International - https://creativecommons.org/licenses/by-sa/4.0
